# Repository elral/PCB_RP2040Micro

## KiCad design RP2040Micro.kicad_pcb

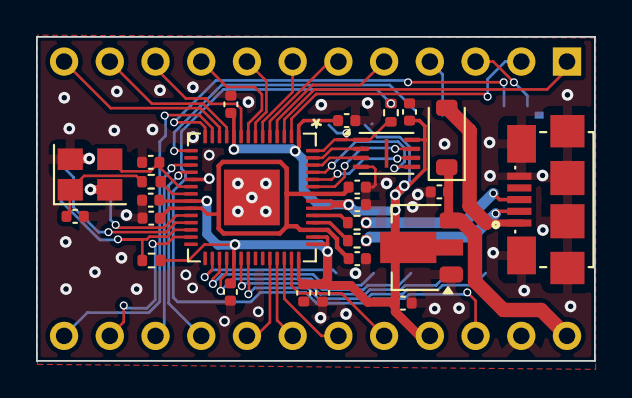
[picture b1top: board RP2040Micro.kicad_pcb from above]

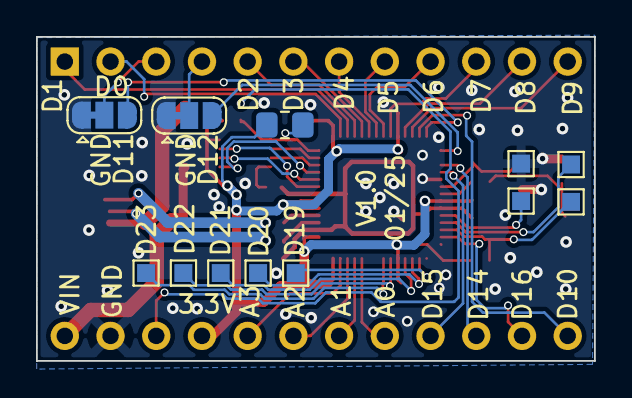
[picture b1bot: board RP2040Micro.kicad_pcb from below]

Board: 2 copper layers, 31.0 x 18.0 mm, 39 parts (12 on the bottom side), 49 nets.

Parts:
C1: 10u; C_0402_1005Metric
C2: 10uF; C_0402_1005Metric
C3, C6, C7, C9, C11, C12, C13, C14, C15: 100n; C_0402_1005Metric
C4, C5: 10pF; C_0402_1005Metric
C8, C10: 1uF; C_0402_1005Metric
D1: D_Schottky; D_SOD-123
J1: Micro USB 10118192-0001LF; AMPHENOL_10118192-0001LF
J3: SWD; TestPoint_Pad_1.0x1.0mm
J4: SWCLK; TestPoint_Pad_1.0x1.0mm
J5: RST; TestPoint_Pad_1.0x1.0mm
J6: GND; TestPoint_Pad_1.0x1.0mm
J12: D19; TestPoint_Pad_1.0x1.0mm
J13: D20; TestPoint_Pad_1.0x1.0mm
J14: D21; TestPoint_Pad_1.0x1.0mm
J15: D22; TestPoint_Pad_1.0x1.0mm
J16: D23; TestPoint_Pad_1.0x1.0mm
JP1, JP2: SolderJumper; SolderJumper-3_P1.3mm_Bridged12_RoundedPad1.0x1.5mm
R1, R2: 1k; R_0402_1005Metric
R3, R4: 27; R_0402_1005Metric
R5: DNF; R_0805_2012Metric_Pad1.20x1.40mm_HandSolder
R6: 10k; R_0402_1005Metric
U1: RP2040; QFN56P40_700X700X90L40X18T310N
U2: AMS1117-3.3; SOT-89-3
U4: W25Q16JVSS; Winbond_USON-8-1EP_3x2mm_P0.5mm_EP0.2x1.6mm
U5: ProMicro
Y1: X322512MSB4SI; Crystal_SMD_3225-4Pin_3.2x2.5mm

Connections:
3.3V: C2.1, C3.1, C9.1, C10.1, C11.1, C12.1, C13.1, C14.1, C15.1, R5.2, R6.1, U1.1 (IOVDD), U1.10 (IOVDD), U1.22 (IOVDD), U1.33 (IOVDD), U1.42 (IOVDD), U1.43 (ADC_AVDD), U1.44 (VREG_IN), U1.48 (USB_VDD), U1.49 (IOVDD), U2.2 (VO), U4.8 (VCC), U5.21 (+5V)
+1V1: C6.1, C7.1, C8.1, U1.23 (DVDD), U1.45 (VREG_VOUT), U1.50 (DVDD)
+5V: D1.2 (A), J1.1 (VUSB)
/RP2040/QSPI_SCLK: U1.52 (QSPI_SCLK), U4.6 (CLK)
/RP2040/QSPI_SD0: U1.53 (QSPI_SD0), U4.5 (DI(IO0))
/RP2040/QSPI_SD1: U1.55 (QSPI_SD1), U4.2 (DO(IO1))
/RP2040/QSPI_SD2: U1.54 (QSPI_SD2), U4.3 (IO2)
/RP2040/QSPI_SD3: U1.51 (QSPI_SD3), U4.7 (IO3)
/RP2040/QSPI_SS: R1.1, R5.1, U1.56 (QSPI_SS), U4.1 (~CS)
/RP2040/SWCLK: J4.1, U1.25 (SWD)
/RP2040/SWD: J3.1, U1.24 (SWCLK)
/RP2040/USB_D+: J1.3 (D+), R3.1
/RP2040/USB_D-: J1.2 (D-), R4.1
/RP2040/USB_D_R+: R3.2, U1.47 (USB_DP)
/RP2040/USB_D_R-: R4.2, U1.46 (USB_DM)
/RP2040/XIN: C4.1, U1.20 (XIN), Y1.3
/RP2040/XOUT: C5.1, R2.2, Y1.1
/RP2040/XOUT_R: R2.1, U1.21 (XOUT)
/RP2040/~RST: J5.1, R6.2, U1.26 (RUN)
A0: U1.38 (GPIO26_ADC0), U5.17 (18/A0)
A1: U1.39 (GPIO27_ADC1), U5.18 (19/A1)
A2: U1.40 (GPIO28_ADC2), U5.19 (20/A2)
A3: U1.41 (GPIO29_ADC3), U5.20 (21/A3)
BOOT_SEL: R1.2, U5.22 (RESET)
D0: U1.2 (GPIO0), U5.2 (0/RX)
D1: U1.3 (GPIO1), U5.1 (1/TX)
D2: U1.4 (GPIO2), U5.5 (2/SDA)
D3: U1.5 (GPIO3), U5.6 (3(PWM)/SCL)
D4: U1.6 (GPIO4), U5.7 (4/A6)
D5: U1.7 (GPIO5), U5.8 (5(PWM))
D6: U1.8 (GPIO6), U5.9 (6(PWM)/A7)
D7: U1.9 (GPIO7), U5.10 (7)
D8: U1.11 (GPIO8), U5.11 (8/A8)
D9: U1.12 (GPIO9), U5.12 (9(PWM)/A9)
D10: U1.13 (GPIO10), U5.13 (10(PWM)/A10)
D11: JP1.3 (B), U1.14 (GPIO11)
D12: JP2.3 (B), U1.15 (GPIO12)
D14: U1.17 (GPIO14), U5.15 (14)
D15: U1.18 (GPIO15), U5.16 (15)
D16: U1.27 (GPIO16), U5.14 (16)
D19: J12.1, U1.30 (GPIO19)
D20: J13.1, U1.31 (GPIO20)
D21: J14.1, U1.32 (GPIO21)
D22: J15.1, U1.34 (GPIO22)
D23: J16.1, U1.35 (GPIO23)
GND: C1.2, C2.2, C3.2, C4.2, C5.2, C6.2, C7.2, C8.2, C9.2, C10.2, C11.2, C12.2, C13.2, C14.2, C15.2, J1.5 (GND), J1.SH1 (SHIELD), J1.SH2 (SHIELD__1), J1.SH3 (SHIELD__2), J1.SH4 (SHIELD__3), J1.SH5 (SHIELD__4), J1.SH6 (SHIELD__5), J6.1, JP1.1 (A), JP2.1 (A), U1.19 (TESTEN), U1.57 (GND), U2.1 (GND), U4.4 (GND), U5.23 (GND), Y1.2, Y1.4
unnamed: JP1.2 (C), U5.3 (GND)
unnamed: JP2.2 (C), U5.4 (GND)
VIN: C1.1, D1.1 (K), U2.3 (VI), U5.24 (VIN)

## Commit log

2025-05-24 exclude KiCad auto generated files
